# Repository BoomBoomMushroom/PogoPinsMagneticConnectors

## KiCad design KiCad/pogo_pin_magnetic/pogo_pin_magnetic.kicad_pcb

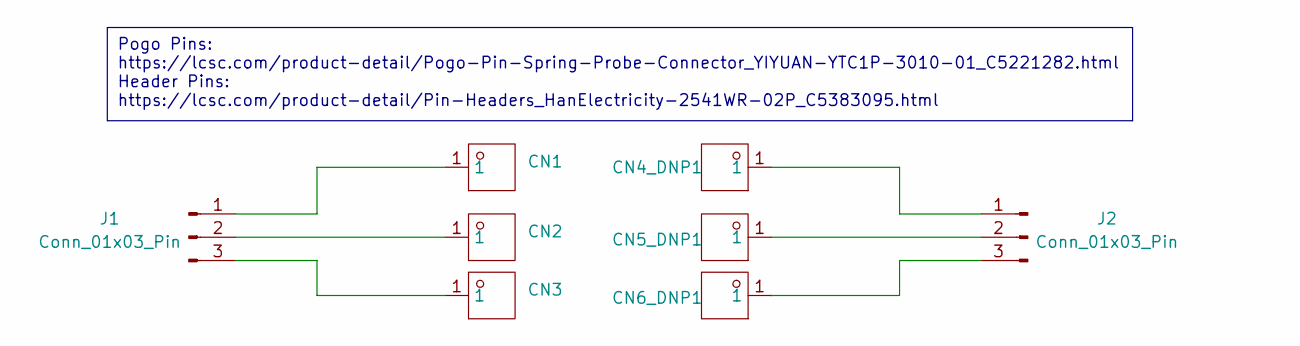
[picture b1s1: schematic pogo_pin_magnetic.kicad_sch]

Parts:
CN1, CN2, CN3, CN4_DNP1, CN5_DNP1, CN6_DNP1: TESTPOINT-SMD_BD2.0_C9900030651; Manufacturer Part YTC1P-3010-01; LCSC Part Name POGO PIN弹簧顶针 贴片连接器
J1, J2: Conn_01x03_Pin; Molex_SPOX_5267-03A_1x03_P2.50mm_Vertical

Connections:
unnamed: CN1.1, J1.1
unnamed: CN2.1, J1.2
unnamed: CN3.1, J1.3
unnamed: CN4_DNP1.1, J2.1
unnamed: CN5_DNP1.1, J2.2
unnamed: CN6_DNP1.1, J2.3

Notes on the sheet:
Pogo Pins: https://lcsc.com/product-detail/Pogo-Pin-Spring-Probe-Connector_YIYUAN-YTC1P-3010-01_C5221282.html Header Pins: https://lcsc.com/product-detail/Pin-Headers_HanElectricity-2541WR-02P_C5383095.html

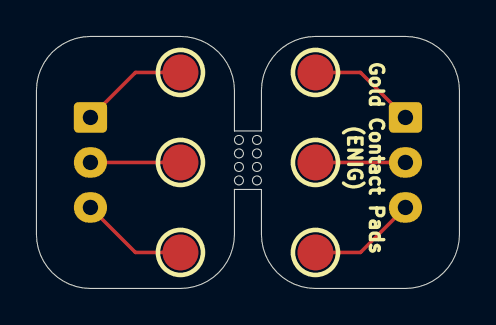
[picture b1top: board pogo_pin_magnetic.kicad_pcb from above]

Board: 2 copper layers, 23.5 x 14.0 mm, 8 parts (0 on the bottom side), 6 nets.

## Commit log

2025-05-21 kicad and blender wip
